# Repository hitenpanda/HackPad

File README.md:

# HackPad v1

A custom parametric mechanical macropad powered by the Seeed Studio XIAO RP2040. Designed, routed in KiCad, and modeled in Fusion 360 for the Hack Club Blueprint initiative.

## Images
### Overall Look

### Schematic

### PCB

### Case Assembly

*The enclosure is a parametric Lower Tray model built perfectly to fit the PCB outline. It uses a 2.0mm offset, 4.0mm standoffs, and 8.0mm walls for a clean "Floating Key" aesthetic.*

---

## Bill of Materials (BOM)

| Part | Quantity | Description / Notes |
| :--- | :---: | :--- |
| **Seeed Studio XIAO RP2040** | 1 | Main Microcontroller (Through-hole) |
| **Mechanical Switches** | 8 | Kailh Choc V2 switches |
| **Keycaps** | 8 | 1U Keycaps to fit each switch |
| **Custom PCB** | 1 | Custom 2-layer PCB |
| **3D Printed Tray (Bottom)** | 1 | 2.0mm thick base with 8.0mm perimeter walls Translucent |
| **Diodes** | 9 | 1N4148 |
| **Mounting Hardware** | 4 | M2 2.2mm screws for securing PCB to tray standoffs and Heatset inserts |
| **Display** | 1 | 0.91" 128x32 OLED Display |
| **Encoder** | 1 | EC11 Rotary Encoder and 1 x 3D-Printed Knob |

---

## 🛠️ Engineering Log & Design Architecture

To give reviewers insight into the design process, here is the technical breakdown of the hardware environment and enclosure architecture.

### Development Stack
*   **EDA (Electronics):** KiCad 9.0 
*   **MCAD (Mechanics):** Autodesk Fusion 360 

### Mechanical Architecture: The "Tray" Design
The current enclosure is modeled as a **Lower Tray**. The design logic is heavily parametric, ensuring that any future changes to the PCB automatically cascade into the 3D printed enclosure.

*   **The Reference PCB (Global Zero):** The PCB was exported from KiCad as a `.step` file. It serves as the absolute "Global Zero" for all sketch planes. All enclosure components are built on the underside of the board (Negative Z-axis) to ensure pin clearance.
*   **The Chassis Floor:** Traced directly from the PCB outer boundary using a **2.0 mm positive offset**. 
    *   *Fixing the "Swiss Cheese" issue:* Initially, the floor generated as a mess of holes because the switch pin cutouts auto-projected from the PCB. Using Timeline Editing, I re-selected only the inner boundary profiles to generate a clean, solid, dust-proof floor.
*   **The Standoffs (Pillars):** Extruded 4.0 mm up and joined to the chassis floor. This provides crucial clearance for bottom-side solder joints and the XIAO MCU.
*   **The Perimeter Walls:** Originally modeled at 16.0 mm. After performing a physical Stack-up Analysis in CAD (Standoff [4mm] + PCB [1.6mm] + Switch Housing), 16.0 mm caused severe interference. It was parametrically reduced to **8.0 mm**, which perfectly covers the rough PCB edge while leaving the switch housings exposed.

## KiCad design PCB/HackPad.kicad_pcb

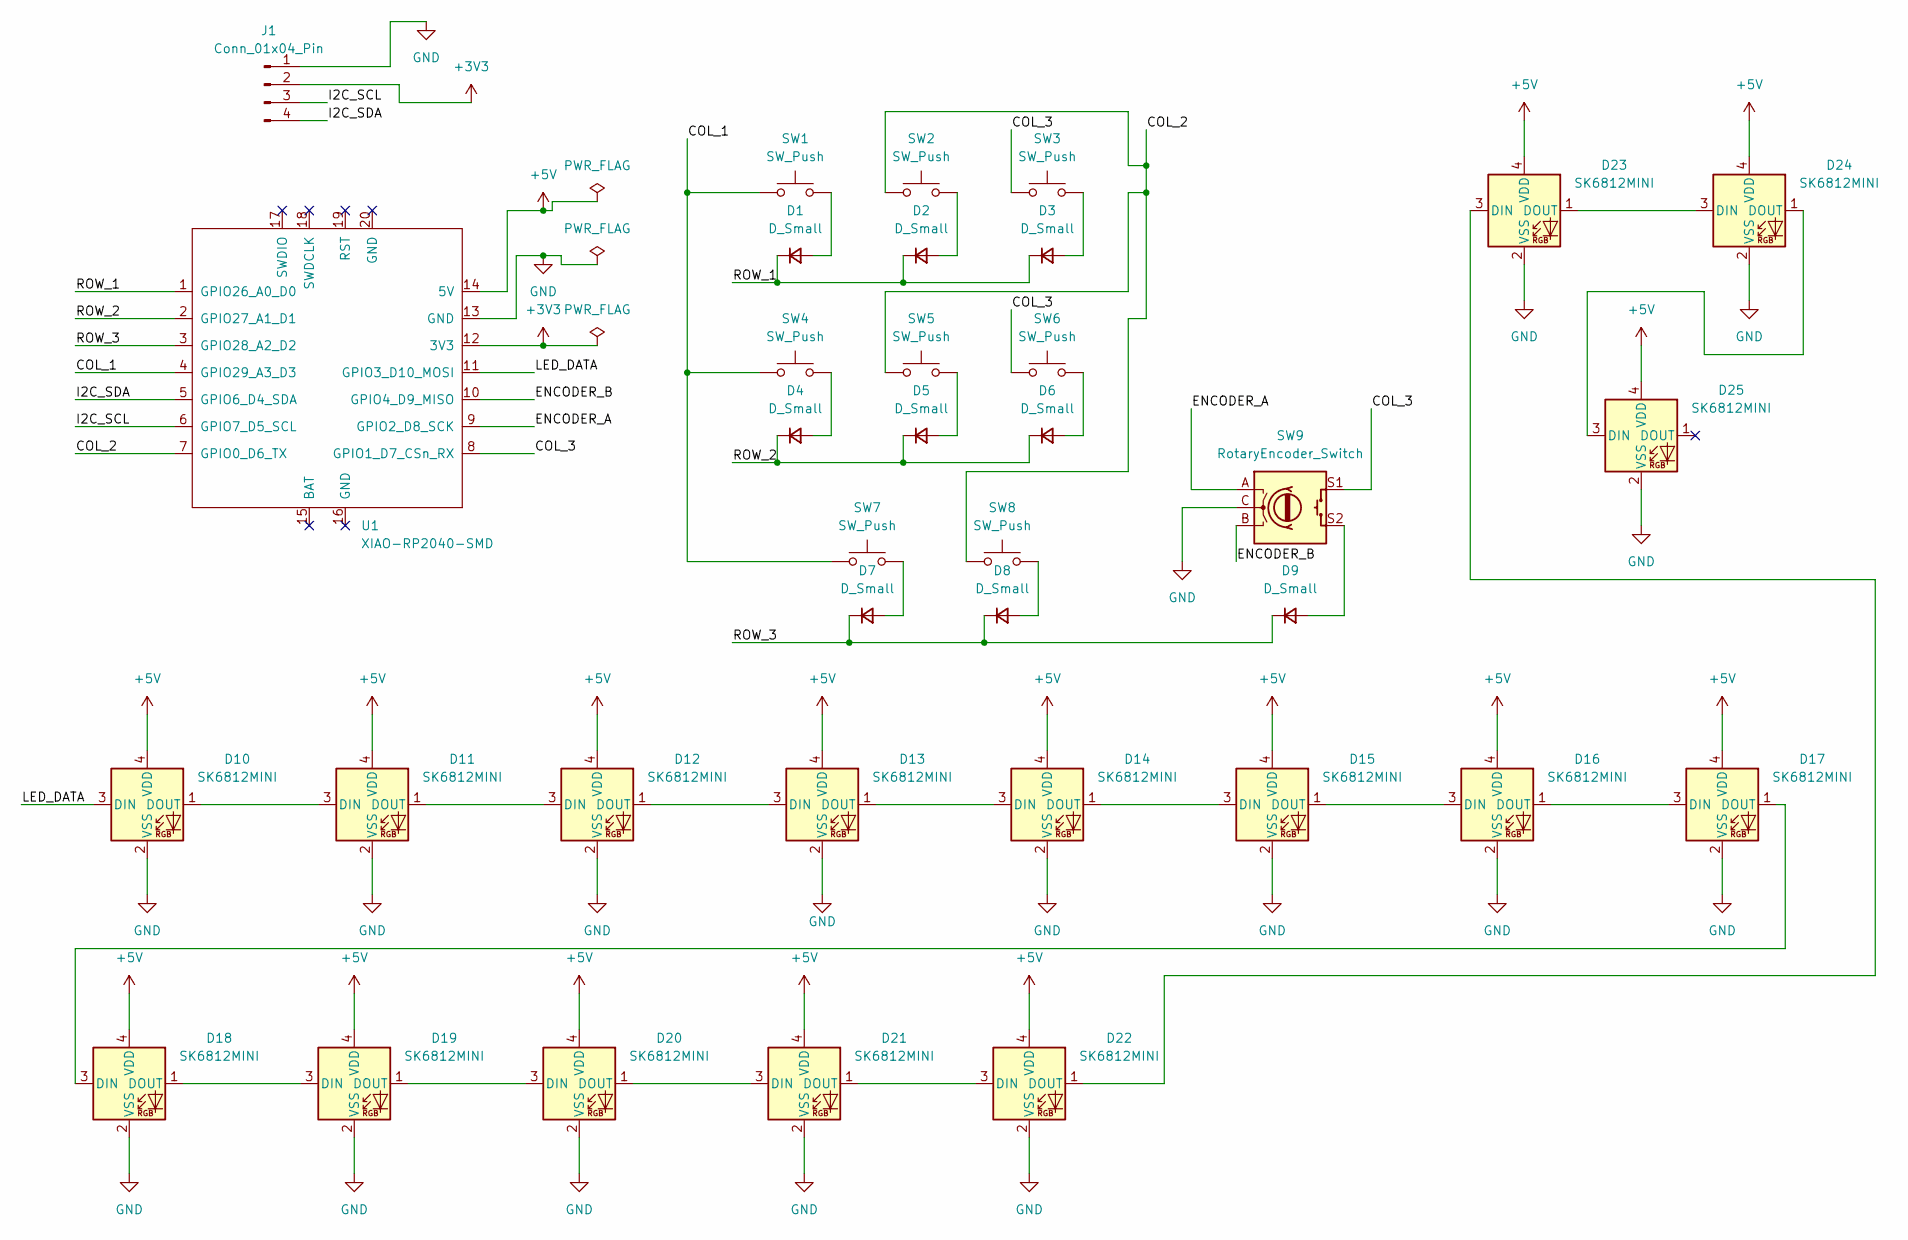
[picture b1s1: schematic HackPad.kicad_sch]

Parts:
D1, D2, D3, D4, D5, D6, D7, D8, D9: D_Small; D_DO-35_SOD27_P7.62mm_Horizontal
D10, D11, D12, D13, D14, D15, D16, D17, D18, D19, D20, D21, D22, D23, D24, D25: SK6812MINI; LED_SK6812MINI_PLCC4_3.5x3.5mm_P1.75mm
J1: Conn_01x04_Pin; PinHeader_1x04_P2.54mm_Vertical
SW1, SW2, SW3, SW4, SW5, SW6, SW7, SW8: SW_Push; SW_Cherry_MX_1.00u_PCB
SW9: RotaryEncoder_Switch; RotaryEncoder_Alps_EC11E-Switch_Vertical_H20mm
U1: XIAO-RP2040-SMD

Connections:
+3V3: J1.2, U1.12 (3V3)
+5V: D10.4 (VDD), D11.4 (VDD), D12.4 (VDD), D13.4 (VDD), D14.4 (VDD), D15.4 (VDD), D16.4 (VDD), D17.4 (VDD), D18.4 (VDD), D19.4 (VDD), D20.4 (VDD), D21.4 (VDD), D22.4 (VDD), D23.4 (VDD), D24.4 (VDD), D25.4 (VDD), U1.14 (5V)
/COL_1: SW1.1, SW4.1, SW7.1, U1.4 (GPIO29_A3_D3)
/COL_2: SW2.1, SW5.1, SW8.1, U1.7 (GPIO0_D6_TX)
/COL_3: SW3.1, SW6.1, SW9.S1, U1.8 (GPIO1_D7_CSn_RX)
/ENCODER_A: SW9.A, U1.9 (GPIO2_D8_SCK)
/ENCODER_B: SW9.B, U1.10 (GPIO4_D9_MISO)
/I2C_SCL: J1.3, U1.6 (GPIO7_D5_SCL)
/I2C_SDA: J1.4, U1.5 (GPIO6_D4_SDA)
/LED_DATA: D10.3 (DIN), U1.11 (GPIO3_D10_MOSI)
/ROW_1: D1.1 (K), D2.1 (K), D3.1 (K), U1.1 (GPIO26_A0_D0)
/ROW_2: D4.1 (K), D5.1 (K), D6.1 (K), U1.2 (GPIO27_A1_D1)
/ROW_3: D7.1 (K), D8.1 (K), D9.1 (K), U1.3 (GPIO28_A2_D2)
GND: D10.2 (VSS), D11.2 (VSS), D12.2 (VSS), D13.2 (VSS), D14.2 (VSS), D15.2 (VSS), D16.2 (VSS), D17.2 (VSS), D18.2 (VSS), D19.2 (VSS), D20.2 (VSS), D21.2 (VSS), D22.2 (VSS), D23.2 (VSS), D24.2 (VSS), D25.2 (VSS), J1.1, SW9.C, U1.13 (GND)
unnamed: D1.2 (A), SW1.2
unnamed: D2.2 (A), SW2.2
unnamed: D3.2 (A), SW3.2
unnamed: D4.2 (A), SW4.2
unnamed: D5.2 (A), SW5.2
unnamed: D6.2 (A), SW6.2
unnamed: D7.2 (A), SW7.2
unnamed: D8.2 (A), SW8.2
unnamed: D9.2 (A), SW9.S2
unnamed: D10.1 (DOUT), D11.3 (DIN)
unnamed: D11.1 (DOUT), D12.3 (DIN)
unnamed: D12.1 (DOUT), D13.3 (DIN)
unnamed: D13.1 (DOUT), D14.3 (DIN)
unnamed: D14.1 (DOUT), D15.3 (DIN)
unnamed: D15.1 (DOUT), D16.3 (DIN)
unnamed: D16.1 (DOUT), D17.3 (DIN)
unnamed: D17.1 (DOUT), D18.3 (DIN)
unnamed: D18.1 (DOUT), D19.3 (DIN)
unnamed: D19.1 (DOUT), D20.3 (DIN)
unnamed: D20.1 (DOUT), D21.3 (DIN)
unnamed: D21.1 (DOUT), D22.3 (DIN)
unnamed: D22.1 (DOUT), D23.3 (DIN)
unnamed: D23.1 (DOUT), D24.3 (DIN)
unnamed: D24.1 (DOUT), D25.3 (DIN)

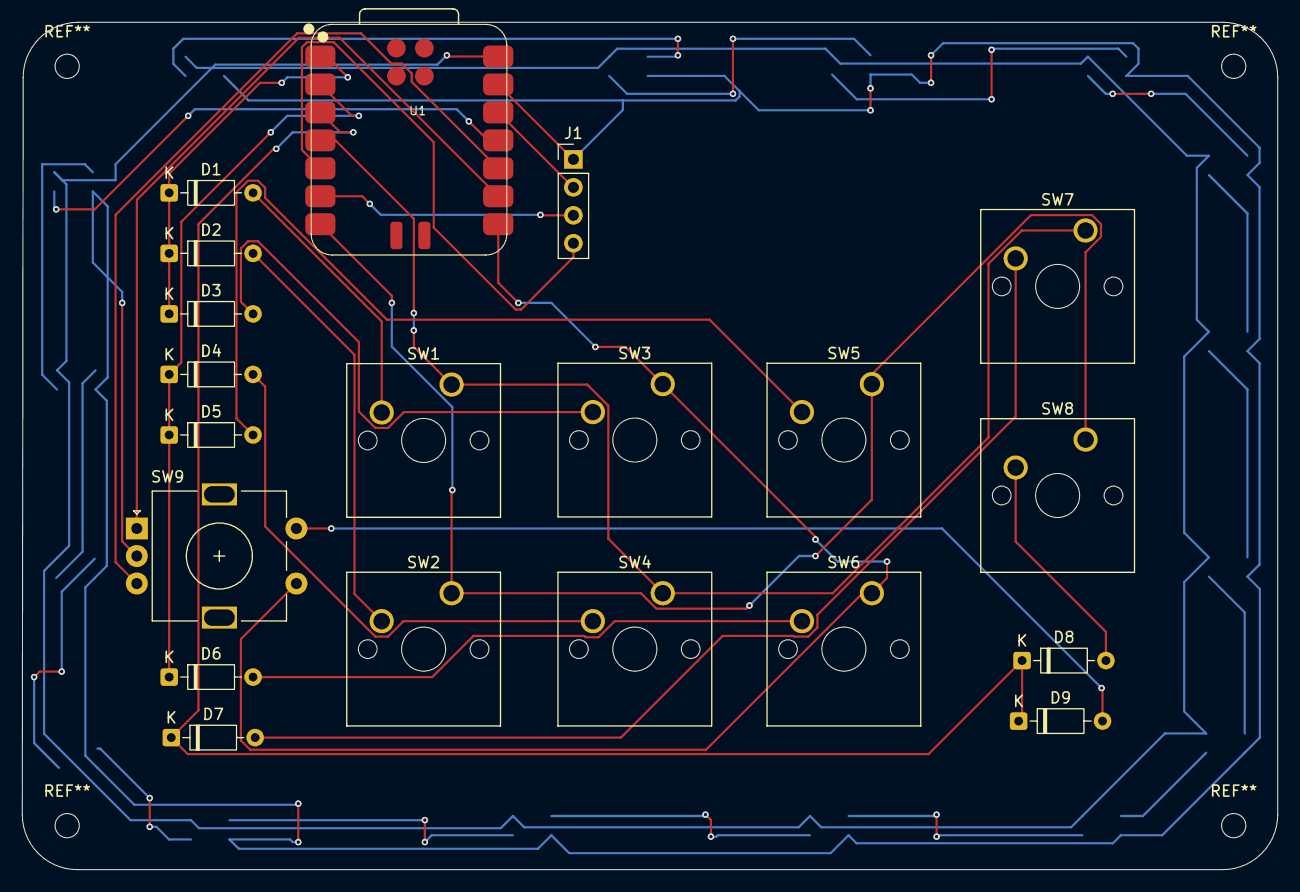
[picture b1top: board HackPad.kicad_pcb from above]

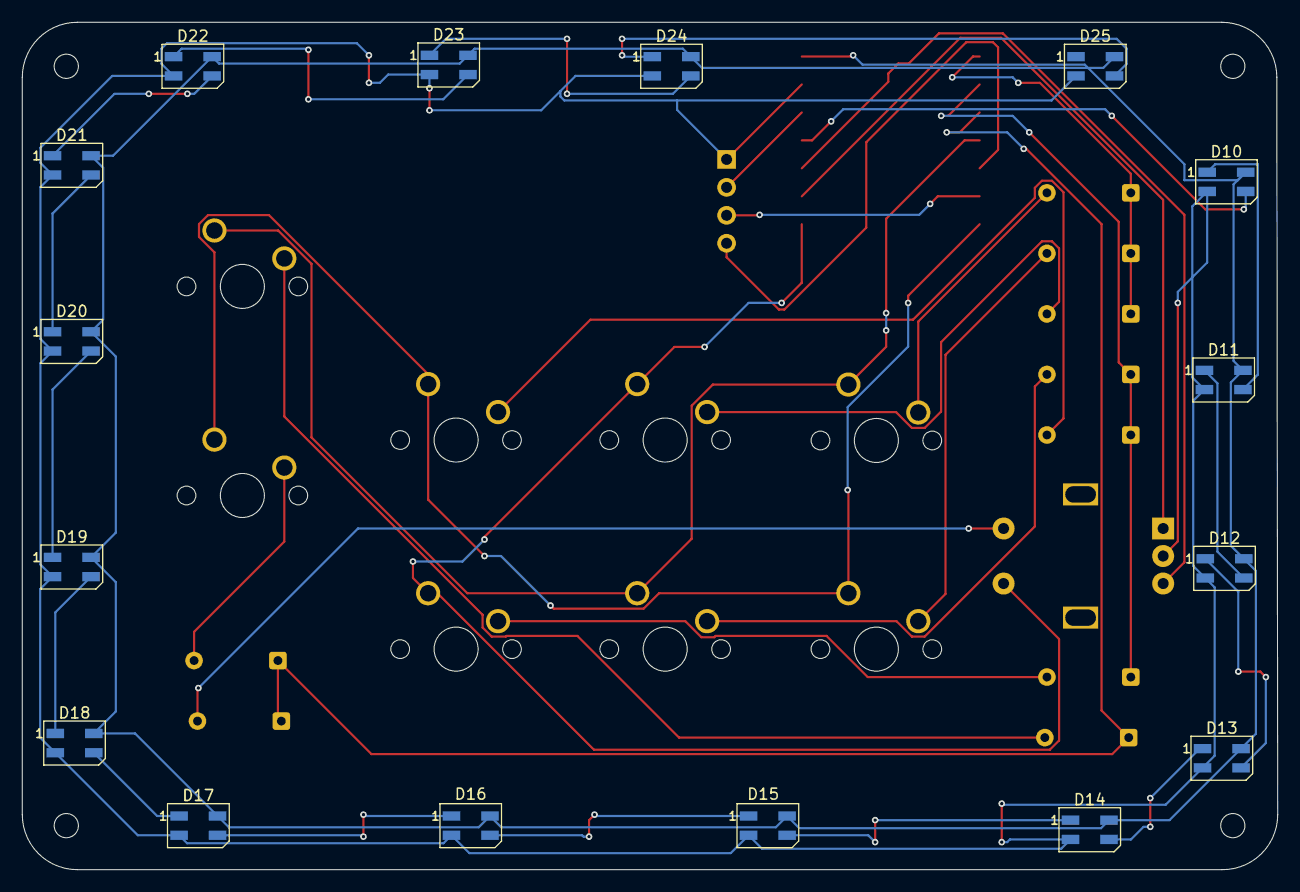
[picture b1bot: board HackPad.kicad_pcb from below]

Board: 2 copper layers, 114.1 x 77.0 mm, 36 parts (16 on the bottom side), 38 nets.

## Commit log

2026-03-26 Initial commit: Open-source HackPad hardware files and production Gerbers
2026-03-28 Created 3D Case, only the bottom part. Will be completing it soon.
2026-03-28 Added the README.md file and corrected the structure.
2026-03-28 Changes: Plan to make a fully closed enclosure dropped, it would be a top naked design.
2026-03-28 Updates regarding design changes.
2026-03-29 After some README.md edits and refactoring.
2026-03-29 README.md updated!
2026-03-30 README.md Updated
2026-03-30 Final update in README before firmware creation.
2026-03-31 The final push for Design Review.
